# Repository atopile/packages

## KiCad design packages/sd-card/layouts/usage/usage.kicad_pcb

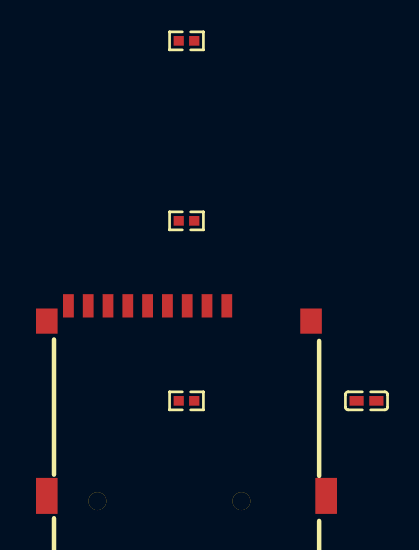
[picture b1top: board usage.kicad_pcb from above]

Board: 2 copper layers, 5 parts (0 on the bottom side), 6 nets, no tracks yet.

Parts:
C4: 100nF ±10% 16V X7R; C0402
Card1: TF-SMD_TF-01A
R4, R5, R6: 10kΩ ±1% 62.5mW; R0402

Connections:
CLK: Card1.5, R6.1
GND: Card1.10, Card1.11, Card1.12, Card1.13
gnd: C4.2, Card1.6
hv: C4.1, Card1.4, R4.2, R5.2, R6.2
pins[6]: Card1.7, R4.1
pins[7]: Card1.8, R5.1

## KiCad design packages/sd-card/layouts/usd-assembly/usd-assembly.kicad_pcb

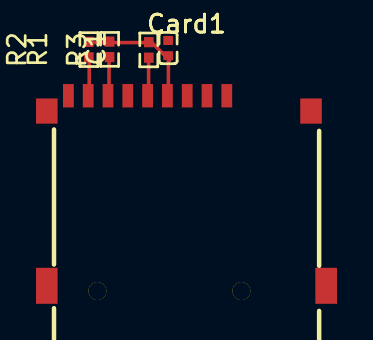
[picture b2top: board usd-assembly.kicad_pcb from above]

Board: 2 copper layers, 5 parts (0 on the bottom side), 6 nets.

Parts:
C1: 100nF; C0402
Card1: TF-SMD_TF-01A
R1, R2, R3: 10kΩ; R0402

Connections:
GND: Card1.10, Card1.11, Card1.12, Card1.13
MISO: Card1.7, R1.1
MOSI: Card1.8, R2.1
SCLK: Card1.5, R3.1
hv: C1.1, Card1.4, R1.2, R2.2, R3.2
lv: C1.2, Card1.6

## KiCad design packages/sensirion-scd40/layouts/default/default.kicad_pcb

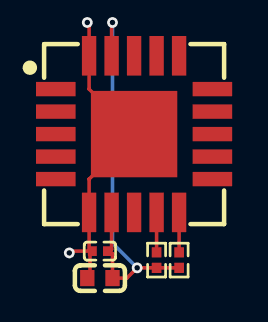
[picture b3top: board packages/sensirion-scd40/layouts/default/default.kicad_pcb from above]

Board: 2 copper layers, 5 parts (0 on the bottom side), 4 nets.

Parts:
C1: 9.999F; C0603
C2: 1F; C0402
R1, R2: 4700Ω; R0402
U1: LGA-20_L10.1-W10.1-P1.25-TL

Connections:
SCL: R1.1, U1.9
SDA: R2.1, U1.10
hv: C1.1, C2.1, R1.2, R2.2, U1.7, U1.19
lv: C1.2, C2.2, U1.6, U1.20, U1.21

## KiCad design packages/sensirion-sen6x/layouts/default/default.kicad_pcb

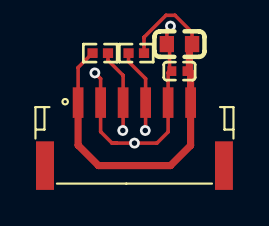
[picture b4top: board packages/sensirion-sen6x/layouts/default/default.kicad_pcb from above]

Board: 2 copper layers, 5 parts (0 on the bottom side), 4 nets.

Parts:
C1: 9.999F; C0603
C2: 1F; C0402
CN1: CONN-TH_SM06B-GHS-TB-LF-SN
R1, R2: 4700Ω; R0402

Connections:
SCL: CN1.4, R1.1
SDA: CN1.3, R2.1
hv: C1.1, C2.1, CN1.1, CN1.6, R1.2, R2.2
lv: C1.2, C2.2, CN1.2, CN1.5
